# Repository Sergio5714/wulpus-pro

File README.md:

# WULPUS Pro Max
## Multi-mode Ultra-Low-Power Wearable Ultrasound Platform
> WULPUS Pro Max adopts the core analog front end of the original [WULPUS PRO design](https://github.com/pulp-bio/wulpus-pro), while extending its analog performance, firmware architecture, host connectivity, and software tooling. The project is independently developed and maintained by [Sergei Vostrikov](https://github.com/Sergio5714) and contributors.

<p align="center">
  
  <br/>
  WULPUS Pro Max module with PolyCMUT transducer.
</p>

## Table of contents

- [Introduction](#introduction)
  - [Hardware photos](#hardware-photos)
  - [System diagram](#system-diagram)
  - [Specifications](#specifications)
- [Clone the repository](#clone-the-repository)
- [Structure of the repository](#structure-of-the-repository)
- [Documentation](#documentation)
- [Build Instructions](#build-instructions)
- [Host setup and operation](#host-setup-and-operation)
  - [WULPUS Pro Max WiFi host PCB (WiFi/USB CDC)](#wulpus-pro-max-wifi-host-pcb-wifiusb-cdc)
  - [WULPUS Pro Max + nRF52 DK + nRF Dongle (BLE)](#wulpus-pro-max--nrf52-dk--nrf-dongle-ble)
- [Citation](#citation)
- [Changelog](#changelog)
- [Authors](#authors)
- [License](#license)
  - [Limitation of Liability](#limitation-of-liability)

# Introduction

WULPUS Pro Max is a modular wearable ultrasound platform for research and
development. It combines a tightly integrated, flexible ultrasound acquisition
front end with a dedicated host board and a mature software stack. Together,
these components provide a complete path from transducer excitation and signal
acquisition to device control, data streaming, visualization, and analysis.

The modular architecture supports both wearable experiments and benchtop
operation:

- **Benchtop operation:** connect a single USB-C cable for power delivery,
  device configuration, and data transfer over USB CDC.
- **Wireless operation:** connect a LiPo battery with a 2-pin JST connector to the
  host board and use Wi-Fi/TCP for seamless, cable-free operation. The host
  board also provides integrated battery charging and protection.

> **Note:** The same USB-C cable can flash and update the entire device without
> external programming tools.

WULPUS Pro Max reliably delivers raw ultrasound data to the host system either
over the air or through a USB cable, with state-of-the-art pulse repetition
frequencies (PRFs) of up to **500 Hz**. The common Python software stack supports
both links, providing the same tools and workflows in either operating mode.

## Hardware photos

<table>
  <tr>
    <td colspan="2" align="center">
      
      <br/>
      Assembled WULPUS Pro Max system
    </td>
  </tr>
  <tr>
    <td width="50%" align="center">
      
      <br/>
      WULPUS PRO Acquisition PCB<br/>
      (development version with test and debug headers)
    </td>
    <td width="50%" align="center">
      
      <br/>
      WULPUS Pro Max WiFi host PCB
    </td>
  </tr>
</table>

## System diagram

<p align="center">
  
  <br/>
  WULPUS Pro Max system diagram
</p>

## Specifications

WULPUS Pro Max builds on the original [WULPUS](https://github.com/Sergio5714/wulpus) platform and keeps the same low-power wearable ultrasound philosophy while extending the hardware and communication options. The table below compares the main features of WULPUS Pro Max with those of the original WULPUS platform.

| Feature | WULPUS | WULPUS Pro Max |
| --- | --- | --- |
| Number of channels | 8, time-multiplexed | **16**, time-multiplexed |
| Supported transducers | PZT transducers | PZT transducers, **CMUTs** |
| Excitation amplitude | 15 V unipolar | **30 V** unipolar |
| Excitation frequency | ~100 kHz to 4 MHz | ~100 kHz to **10 MHz** |
| Transducer biasing | - | Indirect or direct **bias**, **-30 V or 30 V** |
| Analog front-end | 10 dB LNA + 30.8 dB PGA | 6 dB LNA + **70 dB VGA** |
| TGC support | No (fixed gain) | **Yes** (linear profile) |
| Maximum PRF | 50 Hz | **500 Hz** (with WiFi host PCB over Wi-Fi/TCP or USB CDC) |
| Power budget at 50 Hz PRF | <=25 mW | <=40 mW |
| Wireless link | BLE | BLE or **WiFi** (via host) |
| Form factor | 46 x 25 mm footprint | **40 x 20 mm** footprint |

Full WULPUS Pro Max specifications are available in [docs/full_specifications.md](docs/full_specifications.md).

# Clone the repository

Clone the public repository without its private development submodule:

```bash
git clone https://github.com/Sergio5714/wulpus-pro-max.git
```

The `hw/kicad_us_lib` submodule is an internal development library hosted in a
private repository. External users do not have access to it and do not need to
initialize it to use the released fabrication outputs. For editing the KiCad
designs, generate project-specific symbol and footprint libraries from the
symbols and footprints embedded in the corresponding project files. See the
[hardware README](hw/README.md#internal-kicad-library) for details.

Authorized developers can initialize the private submodule after cloning:

```bash
git submodule update --init --recursive
```

# Structure of the repository

The repository is organized into four top-level folders. See the README files
inside them for component-level details.

- [`hw`](hw) — PCB design and fabrication files.
- [`fw`](fw) — embedded firmware source code.
- [`sw`](sw) — Python software, graphical interfaces, and notebooks.
- [`docs`](docs) — project documentation and images.

# Documentation

- [Full system specifications](docs/full_specifications.md)
- [Host board options](docs/host_board_options.md)
- [PCB designs and fabrication](hw/README.md)
- Firmware:
  - [ESP32 host firmware](fw/esp32/README.md)
  - [MSP430 acquisition firmware](fw/msp430/README.md)
  - [Legacy nRF52 BLE firmware](fw/nrf52/README.md)
- [Python software and notebooks](sw/README.md)

For background information about the original WULPUS platform, see the
[legacy WULPUS User Manual](https://github.com/Sergio5714/wulpus/blob/main/docs/wulpus_user_manual.pdf).

# Build Instructions

The WULPUS Pro Max WiFi host PCB provides a one-cable setup and programming
workflow:

1. **Get hardware**

   Order the [Acquisition PCB](docs/images/v1_0/eval_board_main.jpg) and [WiFi host PCB](docs/images/v1_2/wifi_board_top.jpg) using the [PCBWay shared projects](hw/README.md#pcbway-shared-projects), or manufacture and assemble them yourself using the design files, schematics, and bills of materials linked in the [hardware guide](hw/README.md#included-pcb-designs).

2. **Install the host software**

   Follow the [Python software setup instructions](sw/README.md#how-to-get-started) on the host PC.

3. **Compile the firmware images**

   Build the two required firmware images using the dedicated instructions:

   - [Install the ESP-IDF toolchain and compile the ESP32 firmware](fw/esp32/docs/development_guide.md).
   - [Install the MSP430 toolchain and compile the MSP430 firmware](fw/msp430/README.md#build-and-export-firmware).

4. **Connect one USB cable and flash both controllers**

   - Connect the WiFi host PCB to the Acquisition PCB, then connect the host PCB to the PC with a single USB-C cable.
   - First, [flash the ESP32 firmware](fw/esp32/docs/development_guide.md#flash-the-firmware), then reset the board.
   - Then use the same USB connection and the [MSP430 updater GUI](fw/esp32/docs/msp430_update_guide.md#update-the-msp430-over-usb) to program the MSP430 on the Acquisition PCB.

   > No external programmer, adapter board, or additional programming cables are required for this workflow.

# Host setup and operation

WULPUS Pro Max supports multiple host-board configurations. See
[Host board options](docs/host_board_options.md) for a comparison. Instructions
for getting started with each configuration are provided below.

## WULPUS Pro Max WiFi host PCB (WiFi/USB CDC)

1. Connect the [WULPUS Pro Max WiFi host PCB](docs/images/v1_2/wifi_board_top.jpg) to the [Acquisition PCB](docs/images/v1_0/eval_board_main.jpg).
2. Connect the host PCB to the PC with a data-capable USB-C cable. This connection powers both PCBs.
3. Start Jupyter from the `sw` folder:

   ```bash
   uv run jupyter notebook
   ```

4. Open [`wulpus_pro_example.ipynb`](sw/wulpus_pro_example.ipynb) in the browser.
5. For a wired connection, select **USB CDC**, scan for devices, and open the ESP32-C6 port. For a wireless connection, first complete [WiFi provisioning](fw/esp32/docs/wifi_provisioning_guide.md), then select **WiFi** and discover the device.
6. Apply the acquisition configuration in the notebook and start acquisition.

For development with a standalone XIAO ESP32-C6, follow its [wiring and power requirements](fw/esp32/docs/development_guide.md#supported-boards) and the [pin mapping](fw/esp32/docs/development_guide.md#pin-mapping). This setup requires an Acquisition PCB with the MSP430 firmware already programmed.

## WULPUS Pro Max + nRF52 DK + nRF Dongle (BLE)

> The nRF52 BLE option may suit applications that need even lower power
> consumption than the WiFi host solution. It is a legacy, unsupported option
> and is not recommended for new setups. Using it requires additional
> integration work, including manual wiring, external power, and a separate
> programmer for the MSP430.

1. Connect the nRF52 DK to the Acquisition PCB using the pin mapping documented in [fw/nrf52/README.md](fw/nrf52/README.md).
2. Plug in the USB dongle and power the nRF52 DK via USB.
3. Check the dongle connection. The green LED should light up. If it does not, press the reset button on the nRF52 DK and try again.
4. After confirming dongle connectivity, power the Acquisition PCB through the connector or debug pin headers.
5. Start Jupyter from the `sw` folder:

   ```bash
   uv run jupyter notebook
   ```

6. Open [`wulpus_pro_example.ipynb`](sw/wulpus_pro_example.ipynb) in the browser, select **BLE**, and follow the notebook instructions to begin acquisition. Older notebook variants are archived under `sw/legacy`.

# Citation

Please cite our [arXiv preprint](https://arxiv.org/abs/2607.12137):

```bibtex
@article{vostrikov2026wulpuspro,
  title={WULPUS PRO: Multi-mode Ultra-Low-Power Wearable Ultrasound and Array Imaging with CMUT Support},
  author={Vostrikov, Sergei and Villani, Federico and Hirschi, Cedric and Lu, Jinhao and Welsch, Jonas and Angerer, Martin and Cretu, Edmond and Rohling, Robert and Cossettini, Andrea and Benini, Luca},
  journal={arXiv preprint arXiv:2607.12137},
  year={2026},
  url={https://arxiv.org/abs/2607.12137}
}
```

If you would like to cite this repository, please use:

```bibtex
@misc{wulpus_pro_repo_sergio5714_2026,
  title={WULPUS Pro Max: Multi-mode Ultra-Low-Power Wearable Ultrasound Platform (Independently Maintained)},
  author={Vostrikov, Sergei and Villani, Federico and Hirschi, Cedric and Cossettini, Andrea and Benini, Luca},
  year={2026},
  howpublished={GitHub repository},
  url={https://github.com/Sergio5714/wulpus-pro-max}
}
```

# Changelog

See [CHANGELOG.md](CHANGELOG.md) for release notes and main project changes.

# Authors

Since 2025,
[Sergei Vostrikov](https://scholar.google.com/citations?user=a0KNUooAAAAJ&hl=en)
(@Sergio5714) has independently maintained this repository and continued
developing WULPUS Pro Max, with contributions from others.

The initial WULPUS PRO system was developed from 2024 to 2025 as a research
project at the [Integrated Systems Laboratory (IIS)](https://iis.ee.ethz.ch/)
at ETH Zurich by:

- [Sergei Vostrikov](https://scholar.google.com/citations?user=a0KNUooAAAAJ&hl=en) (PCB design, firmware, software, open-sourcing)
- [Federico Villani](https://scholar.google.com/citations?user=5LgLMCEAAAAJ&hl=en) (PCB design, component selection)
- [Cedric Hirschi](https://www.linkedin.com/in/c%C3%A9dric-cyril-hirschi-09624021b/) (firmware, software)
- [Andrea Cossettini](https://scholar.google.com/citations?user=d8O91jIAAAAJ&hl=en) (supervision, project administration)
- [Luca Benini](https://scholar.google.com/citations?hl=en&user=8riq3sYAAAAJ) (supervision, project administration)

Additional contributors to the project were:

- [Sebastian Frey](https://scholar.google.com/citations?user=7jhiqz4AAAAJ&hl=en), ETH Zürich (design review)
- [Alfonso Blanco Fontao](https://www.linkedin.com/in/alfonso-blanco-fontao-b6214726/), ETH Zürich (design review, PCB fabrication coordination)
- [Ciara Giles Doran](https://www.linkedin.com/in/ciaragilesdoran/) (preliminary evaluation of the AD8338 VGA)

# License

The following files are released under Apache License 2.0 (`Apache-2.0`) (see `sw/LICENSE`):

- `sw/`

The hardware designs are released under Solderpad v0.51 (`SHL-0.51`):

- `hw/`

See the [hardware license table](hw/README.md#license) for the applicable license file and copyright holder for each PCB design.

Project-authored firmware code is generally licensed under Apache-2.0, as
identified in the source-file headers. Bundled vendor and third-party code
retains its original license, including BSD-style terms for Texas Instruments
sources and the Nordic Semiconductor license for Nordic SDK sources. See the
license notices and source headers in `fw/esp32/`, `fw/msp430/`, and `fw/nrf52/`
for the terms that apply to each file.

## Limitation of Liability

In no event and under no legal theory, whether in tort (including negligence), contract, or otherwise, unless required by applicable law (such as deliberate and grossly negligent acts) or agreed to in writing, shall any Contributor be liable to You for damages, including any direct, indirect, special, incidental, or consequential damages of any character arising as a result of this License or out of the use or inability to use the Work (including but not limited to damages for loss of goodwill, work stoppage, computer failure or malfunction, or any and all other commercial damages or losses), even if such Contributor has been advised of the possibility of such damages.

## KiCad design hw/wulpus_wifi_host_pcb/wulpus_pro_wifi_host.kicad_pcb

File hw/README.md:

# WULPUS Pro Max PCB design files

This directory contains the PCB designs used by WULPUS Pro Max. The source files are
provided in Altium Designer or KiCad format, depending on the board. Where
available, each project also includes PDF schematics and assembly drawings under
`docs`, and production-ready files under `fabrication_outputs`, including bills
of materials, Gerber files, NC drill files, and pick-and-place files.

## Included PCB designs

### WULPUS PRO Acquisition PCB

Directory: [`wulpus_pro_acq_pcb_dev_board`](wulpus_pro_acq_pcb_dev_board)

The WULPUS PRO Acquisition PCB is the platform's ultrasound acquisition and
pulser board. It contains
the transmit and receive signal paths, high-voltage switching, power supplies,
MSP430 control circuitry, and the host interface. The design sources are provided
in Altium Designer format. This board is required to build a WULPUS Pro Max
system.

### WULPUS Pro Max WiFi host PCB

Directory: [`wulpus_wifi_host_pcb`](wulpus_wifi_host_pcb)

An open-source companion board that integrates wireless communication, power
delivery, and firmware programming for the WULPUS PRO Acquisition PCB. Based
on the [Seeed Studio XIAO ESP32-C6](https://www.seeedstudio.com/Seeed-Studio-XIAO-ESP32C6-p-5884.html),
it supports runtime acquisition configuration and real-time ultrasound data
streaming over Wi-Fi/TCP or native USB CDC at pulse repetition frequencies
(PRFs) of up to 500 Hz. It is the primary host board for WULPUS Pro Max and runs
the [ESP32 firmware](../fw/esp32).

A single USB-C connection powers the complete system and enables wired
communication and firmware updates, including [programming the acquisition
board's MSP430 through integrated JTAG](../fw/esp32/docs/msp430_update_guide.md).
The host supports Wi-Fi provisioning, automatic reconnection, and device
discovery. The platform can also be powered by an external Adafruit battery
with a standard JST connector. USB battery charging is supported, and battery
protection is integrated.

The design sources are provided in KiCad format, together with fabrication and
assembly outputs.

Using the XIAO module provides a stable, actively supported wireless platform
with a proven RF design. Seeed publishes compliance records for the
module, including [FCC Part 15](https://files.seeedstudio.com/Seeed_Certificate/documents_certificate/113991254-FCC.pdf)
and [CE RED](https://files.seeedstudio.com/Seeed_Certificate/documents_certificate/113991254-CE.pdf)
testing. This pre-tested module significantly reduces RF design effort and
compliance risk compared with developing a custom, uncertified RF implementation.

### polyCMUT adapter board

Directory: [`wulpus_polycmut_adapter`](wulpus_polycmut_adapter)

An optional research adapter for connecting polyCMUT transducers to WULPUS. The
design sources are provided in Altium Designer format. This board is not required
for standard WULPUS Pro Max operation.

## Internal KiCad library

The [`kicad_us_lib`](kicad_us_lib) directory is referenced as a Git submodule and
contains the internal KiCad symbols, footprints, and related library assets used
to develop the hardware designs. It is hosted in a private repository and is
intended only for internal development; external users will not have access to
it. The library could not be made publicly open source because some of its
contents are subject to third-party licensing restrictions.

The released KiCad projects embed the symbols and footprints used by each
design. External users are advised to generate their own project-specific symbol
and footprint libraries from the corresponding project files instead of relying
on `kicad_us_lib`. The released fabrication outputs can be used without the
private submodule.

## PCBWay shared projects

For convenient one-click PCB production and assembly, you can use the PCBWay shared projects:

- [WULPUS PRO Acquisition PCB v1.0.0](https://www.pcbway.com/project/shareproject/WULPUS_PRO_Evaluation_board_v1_0_0_992d7510.html)

- [WULPUS PRO WiFi host PCB v1.0.0](https://www.pcbway.com/project/shareproject/WULPUS_PRO_WiFi_host_PCB_7cfe7806.html)

This option is convenient for outsourced PCB production and assembly, with an estimated **~1 month lead time** and a price of about **220 USD** per probe for Acquisition PCB and **40 USD** for the WiFi host PCB, based on mid-2026 pricing.

## License

All three PCB designs are released under the Solderpad Hardware License v0.51
(`SHL-0.51`). They use separate license files because their copyright holders
differ:

| PCB design | Directory | License file | Copyright |
| --- | --- | --- | --- |
| WULPUS PRO Acquisition PCB | [`wulpus_pro_acq_pcb_dev_board`](wulpus_pro_acq_pcb_dev_board) | [`LICENSE_ETH`](LICENSE_ETH) | Copyright (C) 2025 ETH Zurich. All rights reserved. |
| WULPUS polyCMUT adapter | [`wulpus_polycmut_adapter`](wulpus_polycmut_adapter) | [`LICENSE_ETH`](LICENSE_ETH) | Copyright (C) 2025 ETH Zurich. All rights reserved. |
| WULPUS Pro Max WiFi host PCB | [`wulpus_wifi_host_pcb`](wulpus_wifi_host_pcb) | [`LICENSE`](LICENSE) | Copyright (C) 2026 Sergei Vostrikov. All rights reserved. |

The license terms are otherwise identical. The internal `kicad_us_lib`
submodule contains third-party material and is not covered by this table; its
contents retain their respective license terms.

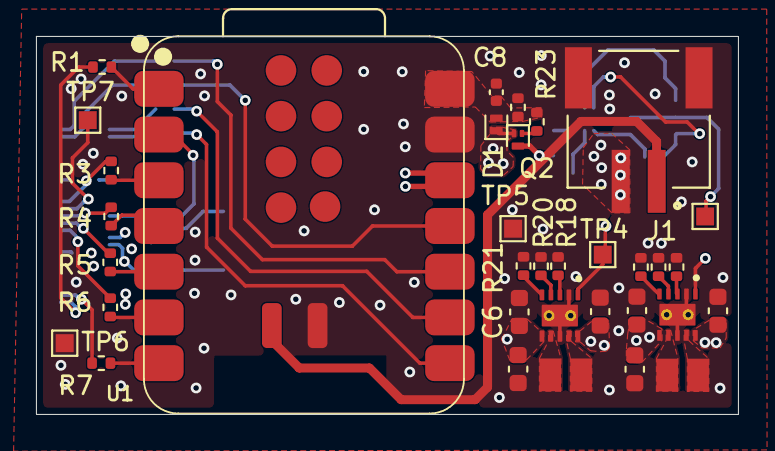
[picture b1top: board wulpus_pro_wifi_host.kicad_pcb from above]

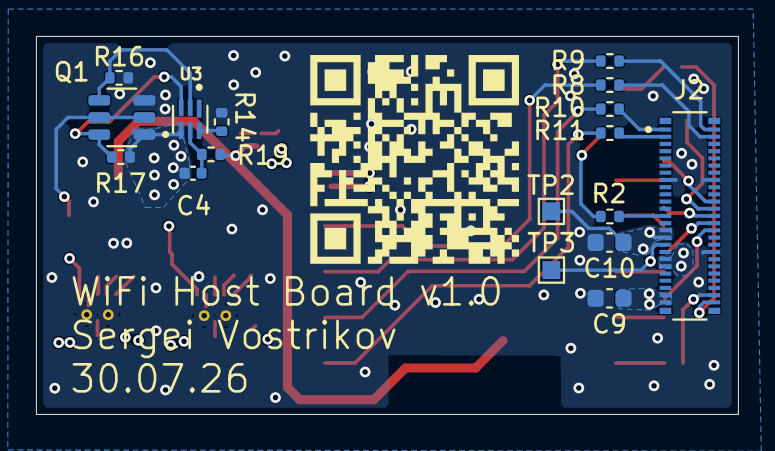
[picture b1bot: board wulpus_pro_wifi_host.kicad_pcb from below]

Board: 4 copper layers, 39.0 x 21.0 mm, 52 parts (18 on the bottom side), 47 nets.

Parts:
C1, C2, C5, C6: 22 uF; C_0603_1608Metric
C3, C7, C9, C10: 10 uF; C_0603_1608Metric
C4, C8: 100 nF; C_0402_1005Metric
D1: LMBR4010BST5G; D_SOD-882
J1: S2B-PH-SM4-TB_LF__SN_; JST_S2B-PH-SM4-TB_LF__SN_
J2: DF40C-50DP-0.4V_51_; HIROSE_DF40C-50DP-0.4V_51_
L1, L2: DFE201612E-2R2M=P2; INDC2016X120N
Q1: FS8205A; SOT95P280X145-6N
Q2: LP0404N3T5G; SOT-883
QR*****: https://github.com/Sergio5714/wulpus-pro; wulpus_pro_qr
R1, R2, R3, R4, R5, R6, R7, R8, R9, R10, R11: 47; R_0402_1005Metric
R12, R13, R18, R20: 0; R_0402_1005Metric
R14: 2.2k; R_0402_1005Metric
R15: 16.2k; R_0402_1005Metric
R16, R17: 5.1M; R_0402_1005Metric
R19: 330; R_0402_1005Metric
R21: 36.5k; R_0402_1005Metric
R22: 100k; R_0402_1005Metric
R23: 100; R_0402_1005Metric
TP1, TP2, TP3, TP4, TP5, TP6, TP7: TestPoint; TestPoint_Pad_1.0x1.0mm
U1: XIAO-ESP32-C6-SMD
U2, U4: TPS63900DSKR; IC_TPS63900DSKR
U3: BQ29700DSER; SON50P150X150X80-6N

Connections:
+3V3: C1.1, C2.1, C10.1, J2.29, J2.31, TP2.1 (1_1), U2.6 (VOUT)
+3V3 ESP: J2.37, J2.39, U1.12 (3V3_OUT)
+5V: C5.1, C6.1, J2.33, TP3.1 (1_1), U4.6 (VOUT)
+V_board: C3.1, C7.1, C9.1, D1.1 (K), J2.47, J2.49, Q2.2 (S), TP4.1 (1_1), U2.1 (EN), U2.10 (VIN), U4.1 (EN), U4.10 (VIN)
/Power/VBAT: J1.1, Q2.3 (D), R19.1, U1.23 (VBAT)
/Power/VBUS: C8.1, D1.2 (A), R22.1, R23.2, U1.14 (VBUS)
/b2b_connector Sheet/MSP_JTAG.RST_n: J2.50, R1.1
/b2b_connector Sheet/MSP_JTAG.TCK: J2.48, R7.1
/b2b_connector Sheet/MSP_JTAG.TDI: J2.28, R5.1
/b2b_connector Sheet/MSP_JTAG.TDO: J2.26, R4.1
/b2b_connector Sheet/MSP_JTAG.TEST: J2.22, R3.1
/b2b_connector Sheet/MSP_JTAG.TMS: J2.30, R6.1
/b2b_connector Sheet/SPI.CLK: J2.4, R8.2
/b2b_connector Sheet/SPI.MISO: J2.2, R9.2
/b2b_connector Sheet/SPI.MOSI: J2.1, R10.2
/b2b_connector Sheet/SPI.SS: J2.3, R11.2
/b2b_connector Sheet/data_rdy: J2.25, R2.1
GND: C1.2, C2.2, C3.2, C5.2, C6.2, C7.2, C8.2, C9.2, C10.2, J1.S1 (SHIELD), J1.S2 (SHIELD), J2.15, J2.16, J2.36, Q1.3, R12.2, R13.2, R14.2, R15.1, R16.2, R18.2, R20.2, R21.1, R22.2, TP5.1 (1_1), TP6.1 (1_1), U1.13 (GND), U1.24 (GND), U2.2 (SEL), U2.8 (GND), U2.11 (EXP), U2.14, U2.15, U4.2 (SEL), U4.8 (GND), U4.11 (EXP), U4.14, U4.15
unnamed: J2.24, TP7.1 (1_1)
unnamed: Q1.2, Q1.5, TP1.1 (1_1)
unnamed: Q2.1 (G), R23.1
unnamed: R1.2, U1.1 (D0)
unnamed: R2.2, U1.2 (D1)
unnamed: R3.2, U1.3 (D2)
unnamed: R4.2, U1.4 (D3)
unnamed: R5.2, U1.5 (D4)
unnamed: R6.2, U1.6 (D5)
unnamed: R7.2, U1.7 (D6)
unnamed: R11.1, U1.8 (D7)
unnamed: R10.1, U1.9 (D8)
unnamed: R9.1, U1.10 (D9)
unnamed: R8.1, U1.11 (D10)
unnamed: R12.1, U2.3 (CFG1)
unnamed: R13.1, U2.4 (CFG2)
unnamed: R15.2, U2.5 (CFG3)
unnamed: L1.2, U2.9 (LX1)
unnamed: L1.1, U2.7 (LX2)
unnamed: C4.1, R19.2, U3.5 (BAT)
unnamed: Q1.4, R16.1, U3.2 (COUT)
unnamed: Q1.6, R17.1, U3.3 (DOUT)
unnamed: R14.1, U3.6 (V-)
unnamed: C4.2, J1.2, Q1.1, R17.2, U3.4 (VSS)
unnamed: R18.1, U4.3 (CFG1)
unnamed: R20.1, U4.4 (CFG2)
unnamed: R21.2, U4.5 (CFG3)
unnamed: L2.2, U4.9 (LX1)
unnamed: L2.1, U4.7 (LX2)

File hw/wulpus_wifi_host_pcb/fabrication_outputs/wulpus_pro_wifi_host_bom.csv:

"Reference","Qty","Value","Exclude from BOM","MANUFACTURER","MP"
"C1,C4","2","22 uF","","Murata Electronics","GRM187R60J226ME15"
"C2,C5,C7,C8","4","10 uF","","Murata Electronics","GRM188R61A106ME69"
"C3,C6","2","100 nF","","Murata Electronics","GCM155R71H104KE02J"
"D1","1","LMBR4010BST5G","","LRC","LMBR4010BST5G"
"J1","1","S2B-PH-SM4-TB_LF__SN_","","JST","S2B-PH-SM4-TB(LF)(SN)"
"J2","1","DF40C-50DP-0.4V_51_","","Hirose Electric Co Ltd","DF40C-50DP-0.4V(51)"
"L1,L2","2","DFE201612E-2R2M=P2","","Murata Electronics","DFE201612E-2R2M=P2"
"Q1","1","FS8205A","","FUXINSEMI","FS8205A"
"Q2","1","LP0404N3T5G","","LRC","LP0404N3T5G"
"R1,R2,R3,R4,R5,R6,R7,R8,R9,R10,R11","11","47","","Yageo","RC0402FR-1347RL"
"R12,R13,R18,R20","4","0","","Yageo","RC0402JR-070RL"
"R14","1","2.2k","","Yageo","RC0402FR-072K2L"
"R15","1","16.2k","","Yageo","RC0402FR-0716K2L"
"R16,R17","2","5.1M","","Yageo","RC0402FR-075M1L"
"R19","1","330","","Yageo","RC0402FR-07330RL"
"R21","1","36.5k","","Yageo","RC0402FR-0736K5L"
"R22","1","100k","","Yageo","RC0402FR-07100KL"
"R23","1","100","","Yageo","RC0402FR-07100RL"
"U1","1","XIAO-ESP32-C6-SMD","","Seeed Studio"," XIAO ESP32C6"
"U2,U4","2","TPS63900DSKR","","Texas Instruments","TPS63900DSKR"
"U3","1","BQ29700DSER","","Texas Instruments","BQ29700DSER"

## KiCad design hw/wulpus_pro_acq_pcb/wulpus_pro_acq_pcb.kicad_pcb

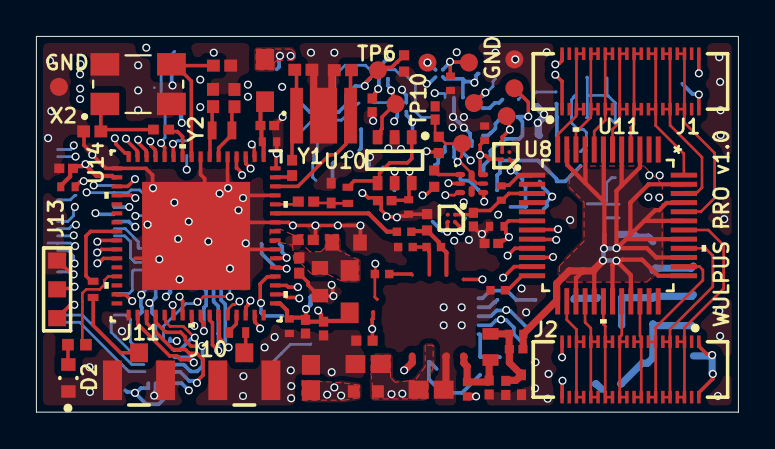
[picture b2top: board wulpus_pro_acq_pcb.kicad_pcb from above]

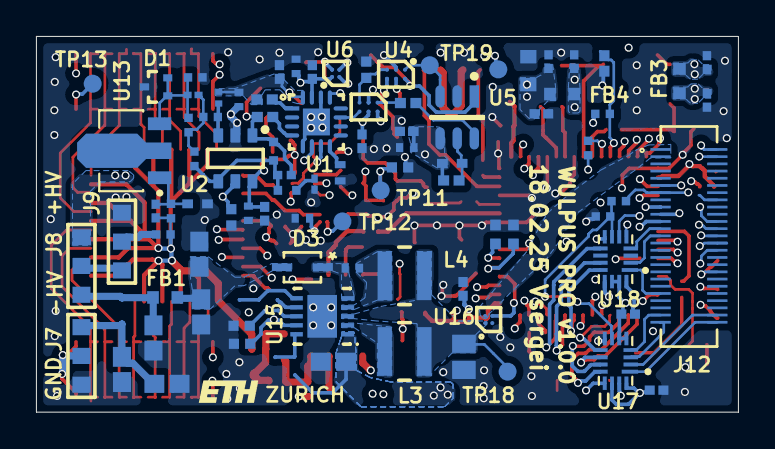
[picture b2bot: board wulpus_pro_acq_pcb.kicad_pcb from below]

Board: 6 copper layers, 39.0 x 20.9 mm, 170 parts (87 on the bottom side), 119 nets.

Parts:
C1: 1.5pf; FP-GJM155-0_05-IPC_C
C2, C17, C18, C19, C21, C22, C23, C29, C31, C33, C51, C52, C53, C73, C74, C75, C76: 0.1 uF; CAPC1005X55X30LL05T10
C3, C6: 10 nf; FP-GRM033-0_03-IPC_B
C4, C7, C10, C12, C43, C45, C46: 1 nf; FP-GRM155-0_05-IPC_B
C5: 3.3 nf; FP-0402-L_1_0_1-W_0_5_0_1-IPC_C
C8, C9, C11, C14, C15, C20, C28, C30, C32, C40, C48, C49, C50: 2.2 uF; FP-C1005-050-0_15-0_1-MFG
C13, C27: 100 pf; FP-0402-L_1_0_1-W_0_5_0_1-MFG
C16, C44, C47: 47 uF; FP-GRM188-0_2-MFG
C24, C25: 10 pf 50V; CAPC1005X55X25LL05T10
C26, C38, C39, C61, C62, C63, C65, C66, C68: 2.2 uF 50V; FP-GRM188-0_2-IPC_B
C41, C42: 47 nf 50V; FP-GRM155-0_05-IPC_C
C54, C55, C57, C58, C59, C60: GJM1555C1H120GB01D; FP-GJM155-0_05-IPC_A
C56: GRM1555C1H102JA01D; FP-GRM155-0_05-IPC_B
C64: 1 uF 50V; FP-GCM21B-0_15-IPC_C
C67: 0.1 uF 50V; FP-GRM155-0_05-MFG
C69, C70, C71, C72: 1 uF 10V; FP-GRM155-0_1-IPC_C
D1: BAV99T-7-F; FP-SOT523-MFG
D2: APHD1608LZGCK; FP-APHD1608LZGCK-MFG
D3: ZHCS400QTA; DIODE_SOD323_DIO
FB1, FB2: BLM18SP101SN1D; FP-BLM18-0_15-t0_8-MFG
FB3, FB4: BLM18SP101SH1D; FP-BLM18-0_15-t0_8-MFG
J1, J2: DF40C-40DS-0.4V(51); FP-DF40C-40DS-0_4V_51-MFG
J7, J8, J9, J13: Solder Jumper; Jumper 3 pins
J10, J11: U.FL-R-SMT-1(10); FP-U_FL-R-SMT-1_10-MFG
J12: DF40HC(3.0)-50DS-0.4V(51); DF40HC3050DS04V51
L1, L2: 742792040; SMD-0805
L3, L4: LQH3NPZ100MMEL; FP-LQH3NPH_ME-MFG
R1: 1.3k; FP-CRCW0402-e3-IPC_B
R2, R3: 2k; FP-ERJ2RK-MFG
R4, R21, R33, R34: 400; FP-CRCW0402-C-e3-MFG
R5: 2.7k; FP-MCS0402-IPC_B
R6, R7, R8, R17, R18, R19, R20, R23, R25, R30, R45, R47: 0 Ohm; FP-CRCW0402-e3-IPC_C
R9: 47k; FP-RMCF0201-MFG
R10, R11, R12, R14, R16, R22, R43, R44: 10k; FP-CRCW0402-e3-IPC_B
R13: 51; FP-CRCW0402-e3-IPC_C
R15: 0 Ohm; FP-ERJ-3GEY0R00V-MFG
R26, R29: 390k; FP-RC1005-MFG
R27, R28, R46: 100k; FP-ERJ2RK-IPC_C
R31, R32: CRCW04021M00FKED; FP-CRCW0402-e3-MFG
R35, R38: RC0402JR-0722RL; RESC1005X40X25NL05T10
R36: CPF0402B324RE1; RESC1005X35X20ML05T10
R37: CRCW040247K0FKED; FP-CRCW0402-e3-IPC_C
TP1, TP2, TP3, TP4, TP5, TP6, TP7, TP8, TP9, TP10, TP11, TP12, TP13, TP18, TP19, TP20: TP-SM-C-100
U1: AD8338ACPZ-R7; FP-CP-16-22-IPC_C
U2, U10: OPA836IDBVT; DBV0006A_L
U3: TPL0501-100RSER; TI-RSE8_V
U4, U7: TS5A3159AYZPR; BGA6C50P2X3_89X139X50
U5: LTC5507ES6#TRMPBF; FP-LTC5507ES6#TRMPBF-IPC_B
U6, U8, U12, U16: TPS22916CYFPR; BGA4C40P2X2_78X78X50
U11: HV2707T-C/R8X; LQFP48_7X7MC_MCH
U13: MD0100N8-G; AMP_PHA-1+
U14: MSP430FR5043IRGCT; RGC0064G
U15: LT3463EDD#PBF; LT-DD-10_V
U17, U18: SN74AVC4T774RSVR; QFN40P260X180X55-16N
X2: FY0800018; XTAL_ECS-80-18-30B-AGN-TR
Y1: AWSCR-8.00CV-T; AWSCR-8.00CV-T_ABR
Y2: ABS05-32.768KHZ-9-T; FP-ABS05-MFG

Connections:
+5V: C40.2, J12.9, U12.A2 (VIN)
+HV: C26.1, C66.1, FB2.2, J8.1
+VBAT: J12.1, J12.2, U16.A2 (VIN)
+VCC_MSP430: C32.1, C33.2, C49.2, C50.2, C52.1, C53.1, C70.1, C73.1, C75.1, FB3.2, J12.37, L1.1, L2.1, R37.1, TP19.1 (1_1), U11.18 (VLL), U14.18 (DVCC1), U14.49 (DVCC3), U17.13 (VCCB), U18.13 (VCCB)
+VCC_MSP430_CONN: C69.1, FB3.1, J12.10
+V_HV_MUX: C30.1, C31.2, U11.15 (VDD), U12.A1 (VOUT)
+V_IN_HV: C64.1, L3.1, L4.1, TP18.1 (1_1), U15.3 (VIN), U16.A1 (VOUT)
+V_IO_IN: C74.1, C76.1, J12.6, J12.7, J13.3, R46.2, U17.5 (DIR3), U17.6 (DIR4), U17.14 (VCCA), U17.16 (DIR2), U18.14 (VCCA), U18.15 (DIR1)
+V_PREAMP: C14.1, C18.2, U2.6 (VS+), U8.A1 (VOUT)
+V_RX: C9.2, C11.2, C12.2, C13.1, C16.1, C17.2, C20.1, C21.2, C22.2, C23.2, C28.1, C29.2, C72.1, FB4.2, TP20.1 (1_1), U3.7 (VDD), U4.B2 (V+), U5.4 (VCC), U6.A2 (VIN), U7.B2 (V+), U8.A2 (VIN), U10.6 (VS+)
+V_RX_CONN: C71.1, FB4.1, J12.11
+V_VGA: C15.1, C19.2, U1.6 (MODE), U1.15 (VBAT), U6.A1 (VOUT)
-HV: C62.1, FB1.2, J8.3
/U_host_connector/HOST_DATA_RDY: U14.42 (P6.0_TA0CLK_COUT), U18.11 (B2)
/U_host_connector/HOST_LINK_RDY: U14.41 (P5.7_TA0.2_UCB1STE), U18.12 (B1)
/U_host_connector/HOST_SPARE: U14.43 (P6.4_MCLK), U18.9 (B4)
/U_host_connector/HOST_SPI_CS: U14.37 (P5.3_TB0.3_UCA2STE), U17.9 (B4)
/U_host_connector/I2C_A_SCL: J12.36, R45.2
/U_host_connector/LVL_SHIFTER_EN: R46.1, R47.2, U17.7 (~OE), U18.7 (~OE)
/U_host_connector/MOSI: U3.2 (DIN), U11.19 (DIN)
/U_host_connector/MSP_CS: J12.12, U18.4 (A4)
/U_host_connector/MSP_DR1: J12.13, U18.2 (A2)
/U_host_connector/MSP_DR2: J12.21, U18.1 (A1)
/U_host_connector/SCLK: U3.5 (SCLK), U11.20 (CLK)
/U_host_connector/SPI_B_CLK: J12.27, U17.2 (A2)
/U_host_connector/SPI_B_CS: J12.24, U17.4 (A4)
/U_host_connector/SPI_B_MISO: J12.26, U17.1 (A1)
/U_host_connector/SPI_B_MOSI: J12.25, U17.3 (A3)
/U_hv_mux_tr_sw/BOT_EL: J1.1, J1.2, J1.39, J1.40, J2.1, J2.2, J2.39, J2.40, J7.2, TP13.1 (1_1)
/U_hv_mux_tr_sw/CH_0: J1.5, J1.6, J1.7, J1.8, U11.12 (SW0A)
/U_hv_mux_tr_sw/CH_1: J1.9, J1.10, J1.11, J1.12, U11.10 (SW1A)
/U_hv_mux_tr_sw/CH_2: J1.13, J1.14, J1.15, J1.16, U11.8 (SW2A)
/U_hv_mux_tr_sw/CH_3: J1.17, J1.18, J1.19, J1.20, U11.6 (SW3A)
/U_hv_mux_tr_sw/CH_4: J1.21, J1.22, J1.23, J1.24, U11.4 (SW4A)
/U_hv_mux_tr_sw/CH_5: J1.25, J1.26, J1.27, J1.28, U11.48 (SW5A)
/U_hv_mux_tr_sw/CH_6: J1.29, J1.30, J1.31, J1.32, U11.46 (SW6A)
/U_hv_mux_tr_sw/CH_7: J1.33, J1.34, J1.35, J1.36, U11.44 (SW7A)
/U_hv_mux_tr_sw/CH_8: J2.5, J2.6, J2.7, J2.8, U11.42 (SW8A)
/U_hv_mux_tr_sw/CH_9: J2.9, J2.10, J2.11, J2.12, U11.40 (SW9A)
/U_hv_mux_tr_sw/CH_10: J2.13, J2.14, J2.15, J2.16, U11.38 (SW10A)
/U_hv_mux_tr_sw/CH_11: J2.17, J2.18, J2.19, J2.20, U11.34 (SW11A)
/U_hv_mux_tr_sw/CH_12: J2.21, J2.22, J2.23, J2.24, U11.32 (SW12A)
/U_hv_mux_tr_sw/CH_13: J2.25, J2.26, J2.27, J2.28, U11.30 (SW13A)
/U_hv_mux_tr_sw/CH_14: J2.29, J2.30, J2.31, J2.32, U11.28 (SW14A)
/U_hv_mux_tr_sw/CH_15: J2.33, J2.34, J2.35, J2.36, U11.26 (SW15A)
/U_hv_mux_tr_sw/RX_OUT: C6.1, D1.1, D1.2, R6.1, R28.2, U13.3 (B)
/U_hv_mux_tr_sw/TR_SW_IN: C42.1, R25.1, R29.2, U13.1 (A)
/U_hv_mux_tr_sw/TX_HV_PULSE_IN: C25.2, C41.2, R15.2, R26.1, R30.2
/U_hv_mux_tr_sw/TX_RX: C41.1, C42.2, R25.2, R27.1, R30.1, U11.3 (SW4B), U11.5 (SW3B), U11.7 (SW2B), U11.9 (SW1B), U11.11 (SW0B), U11.25 (SW15B), U11.27 (SW14B), U11.29 (SW13B), U11.31 (SW12B), U11.33 (SW11B), U11.37 (SW10B), U11.39 (SW9B), U11.41 (SW8B), U11.43 (SW7B), U11.45 (SW6B), U11.47 (SW5B)
/U_msp430/ADC_IN: C27.2, C43.1, R21.2
/U_msp430/AVCC1: C48.2, C51.1, L2.2, U14.1 (AVCC1)
/U_msp430/CH0_IN: C43.2, U14.60 (CH0_IN)
/U_msp430/CH0_OUT: R13.1, U14.59 (CH0_OUT)
/U_msp430/CH1_OUT: R32.1, U14.54 (CH1_OUT)
/U_msp430/ENV_DET_EN: R10.1, TP6.1 (1_1), U4.A2 (IN), U5.1 (~SHDN), U7.A2 (IN), U14.25 (P1.4_TB0.4_UCB0STE_A2_C2)
/U_msp430/HFXIN: C55.2, U14.9 (PJ.6_HFXIN_USSXT_BOUT), X2.3 (OUT/IN)
/U_msp430/HFXOUT: R35.2, U14.10 (PJ.7_HFXOUT)
/U_msp430/HV_MUX_CLR: U11.22 (CLR), U14.31 (P4.3_UCA0SIMO_UCA0TXD)
/U_msp430/HV_MUX_LE: U11.21 (LE), U14.46 (P7.0_TA1.0_TA1.2_XPB0)
/U_msp430/HV_MUX_PWR_EN: TP12.1 (1_1), U12.B2 (ON), U14.44 (P6.5_SMCLK)
/U_msp430/HV_NEG_EN: R44.1, U14.51 (P3.4_SMCLK_DMAE0), U15.8 (~SHDN2)
/U_msp430/HV_POS_EN: R43.1, U14.50 (P3.3_MCLK_TB0.3_XPB1), U15.9 (~SHDN1)
/U_msp430/HV_PWR_EN: U14.52 (P3.5_ACLK_COUT), U16.B2 (ON)
/U_msp430/JTAG_RESET_N: C56.1, R37.2, U14.12 (RST__NMI_SBWTDIO_N)
/U_msp430/LED_MSP430: R36.1, U14.29 (P4.1_UCA0CLK_TB0.4_UCA3SOMI_UCA3RXD)
/U_msp430/LFXIN: C60.2, U14.6 (PJ.4_LFXIN), Y2.1
/U_msp430/LFXOUT: C58.2, U14.7 (PJ.5_LFXOUT), Y2.2
/U_msp430/LP_FILT_EN: R22.1, TP11.1 (1_1), U10.5 (~PD), U14.27 (P3.1_TA1CLK_TB0.1_MTIF_OUT_IN)
/U_msp430/PREAMP_EN: R12.1, U2.5 (~PD), U14.20 (P1.3_UCA1SOMI_UCA1RXD_TA1.1_A9_C9)
/U_msp430/PREAMP_PWR_EN: TP5.1 (1_1), U8.B2 (ON), U14.26 (P1.5_TB0.5_UCB0CLK_A3_C3)
/U_msp430/PULS_HIZ_EN: R16.2, U14.47 (P6.2_TB0CLK)
/U_msp430/PVCC: C44.2, C45.2, C46.1, C47.1, L1.2, U14.56 (PVCC), U14.57 (PVCC)
/U_msp430/TRIG_OUT: R33.2, U14.45 (P6.6_ACLK)
/U_msp430/USSXTIN: C59.2, U14.62 (USSXTIN), Y1.3
/U_msp430/USSXTOUT: R38.2, U14.63 (USSXTOUT)
/U_msp430/UUPS_TRIG_IN: R34.2, U14.24 (P1.7_USSTRG_UCA3CLK_UCB0SOMI_UCB0SCL)
/U_msp430/VGA_GAIN_CS: U3.3 (~CS), U14.4 (P1.1_UCA1STE_TA4.0_A1_C1_VREF+_VeREF+)
/U_msp430/VGA_GAIN_RC_EN: R5.1, U14.3 (P1.0_UCA1CLK_TA1.0_A0_C0_VREF-_VeREF-)
/U_msp430/VGA_GAIN_RC_SINK: R1.1, U14.2 (P2.2_COUT_UCA0CLK_A14_C14)
/U_msp430/VGA_PWR_EN: TP4.1 (1_1), U6.B2 (ON), U14.19 (P1.2_UCA1SIMO_UCA1TXD_TA1.0_A8_C8)
/U_rx_path/ENV_OUT: TP3.1 (1_1), U4.A1 (NO), U5.3 (VOUT)
/U_rx_path/PCAP: C12.1, C13.2, U5.5 (PCAP)
/U_rx_path/RF_BYPASS: R11.1, U4.C1 (NC), U7.C1 (NC)
/U_rx_path/RF_IN_ENV: C10.1, U7.A1 (NO)
/U_rx_path/SIG_OUT: TP10.1 (1_1), U4.C2 (COM), U10.3 (VIN+)
/U_rx_path/VGA_GAIN: C5.1, R1.2, TP1.1 (1_1), U1.7 (GAIN), U3.6 (W), U3.8 (L)
/U_rx_path/VGA_IN: C1.2, C4.1, R3.2, TP2.1 (1_1), U2.1 (VOUT)
/U_rx_path/VGA_OUT: U1.11 (OUTP), U7.C2 (COM)
/U_rx_path_lp_filter/BUF_OUT: R21.1, U10.1 (VOUT), U10.4 (VIN-)
/U_tx_path/PULSER_IN_A: R13.2, R14.2, R17.1
/U_tx_path/PULSER_IN_B: R17.2, R18.2
/U_tx_path/PULSER_OUT_A: C24.2, R15.1, R20.1
GND: C2.1, C3.1, C5.2, C8.2, C9.1, C11.1, C14.2, C15.2, C16.2, C17.1, C18.1, C19.1, C20.2, C21.1, C22.1, C23.1, C24.1, C25.1, C26.2, C27.1, C28.2, C29.1, C30.2, C31.1, C32.2, C33.1, C38.2, C39.2, C40.1, C44.1, C45.1, C46.2, C47.2, C48.1, C49.1, C50.1, C51.2, C52.2, C53.2, C54.1, C55.1, C56.2, C57.1, C58.1, C59.1, C60.1, C61.2, C62.2, C63.2, C64.2, C65.2, C66.2, C68.2, C69.2, C70.2, C71.2, C72.2, C73.2, C74.2, C75.2, C76.2, D1.3, D2.1 (C), J7.3, J9.1, J10.2 (GND), J10.3 (GND), J11.2 (GND), J11.3 (GND), J12.18, J12.33, J12.43, J13.1, R4.1, R10.2, R11.2, R12.2, R14.1, R16.1, R18.1, R22.2, R23.1, R26.2, R28.1, R29.1, R31.2, R32.2, R43.2, R44.2, R47.1, TP8.1 (1_1), TP9.1 (1_1), U1.5 (COMM), U1.14 (OFSN), U1.17 (EP), U2.2 (VS-), U3.4 (GND), U4.B1 (GND), U5.2 (GND), U6.B1 (GND), U7.B1 (GND), U8.B1 (GND), U10.2 (VS-), U11.13 (GND), U11.17 (DGND), U12.B1 (GND), U14.5 (AVSS2), U14.8 (AVSS3), U14.17 (DVSS1), U14.33 (DVSS2), U14.48 (DVSS3), U14.55 (PVSS), U14.58 (PVSS), U14.61 (AVSS4), U14.64 (AVSS1), U14.65 (EP), U15.11 (EP), U16.B1 (GND), U17.8 (GND), U17.15 (DIR1), U18.5 (DIR3), U18.8 (GND), U18.16 (DIR2), X2.2 (GND), X2.4 (GND), Y1.2
unnamed: C3.2, R2.1
unnamed: C6.2, R6.2, R7.1, R8.1
unnamed: C38.1, C39.1, J7.1
unnamed: C57.2, R38.1, Y1.1
unnamed: D2.2 (A), R36.2
unnamed: J8.2, J9.3
unnamed: J9.2, R27.2
unnamed: J10.1 (SIG), R33.1
unnamed: J11.1 (SIG), R34.1
unnamed: R4.2, U1.8 (DETO)
unnamed: C4.2, U1.4 (INMR)
unnamed: C7.2, U1.1 (INPR)
unnamed: R8.2, R9.2, U2.3 (VIN+)
unnamed: C1.1, R2.2, R3.1, R7.2, U2.4 (VIN-)
unnamed: R5.2, U3.1 (H)
unnamed: C10.2, U5.6 (RFIN)
unnamed: R23.2, U11.24 (RGND)
unnamed: R31.1, U14.53 (CH1_IN)
unnamed: C67.1, D3.1, U15.5 (D2)
unnamed: L3.2, U15.2 (SW1)
unnamed: C67.2, L4.2, U15.4 (SW2)
unnamed: J13.2, U18.6 (DIR4)
unnamed: C54.2, R35.1, X2.1 (IN/OUT)
VGA_VREF: C2.2, C7.1, C8.1, R9.1, TP7.1 (1_1), U1.13 (VAGC), U1.16 (VREF)
VOUT_NEG: C61.1, C68.1, D3.2, FB1.1
VOUT_POS: C63.1, C65.1, FB2.1, U15.1 (VOUT1)

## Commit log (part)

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2026-06-29 Updating spressif SDK, migrating to XIAO C6 board
